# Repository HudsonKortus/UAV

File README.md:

<div align="center">
    
</div>

# UAV 2.0
UAV 2.0 is a thrust vector controlled, electric ducted fan powered UAV. I started this project in June of 2020, and have been working on it off and on ever since. Over the course of this project I have become a better programmer, more confident in CAD, I have learned how to aerodynamically simulate parts in CFD, and taught myself how to make custom PCBs using EAGLE. There is still work that needs to be done to get the UAV to a place where it can fly. 

# ABOUT
The UAV utilizes moveable thrust vanes which are in the exhaust stream of the electric ducted fan to stabilize the vehicle. The control system is a very basic PID loop, but I plan to move to an LQG controller which will allow the UAV to hover in one place. All the electronics are custom. I used a Teensy 4.0 for the microcontroller, and BMI 088 for the gyroscope and acceleration reading. The electric ducted fan is a basic one I got off Amazon which runs off a 4s, 4000mAh lipo. The electric ducted fan produces a little over 1.2kg of static thrust which currently is not enough to lift the vehicle.

# TODO
 * make UAV be tethered to battery instead of carrying it because the battery is too heavy
 * change form using thrust vanes to gimbaling the motor because thrust vanes cannot be practically mathematically characterizes
 * rewrite code to be more object oriented
 * replace the PID controller with an LQG controller
 * make FAA compliant

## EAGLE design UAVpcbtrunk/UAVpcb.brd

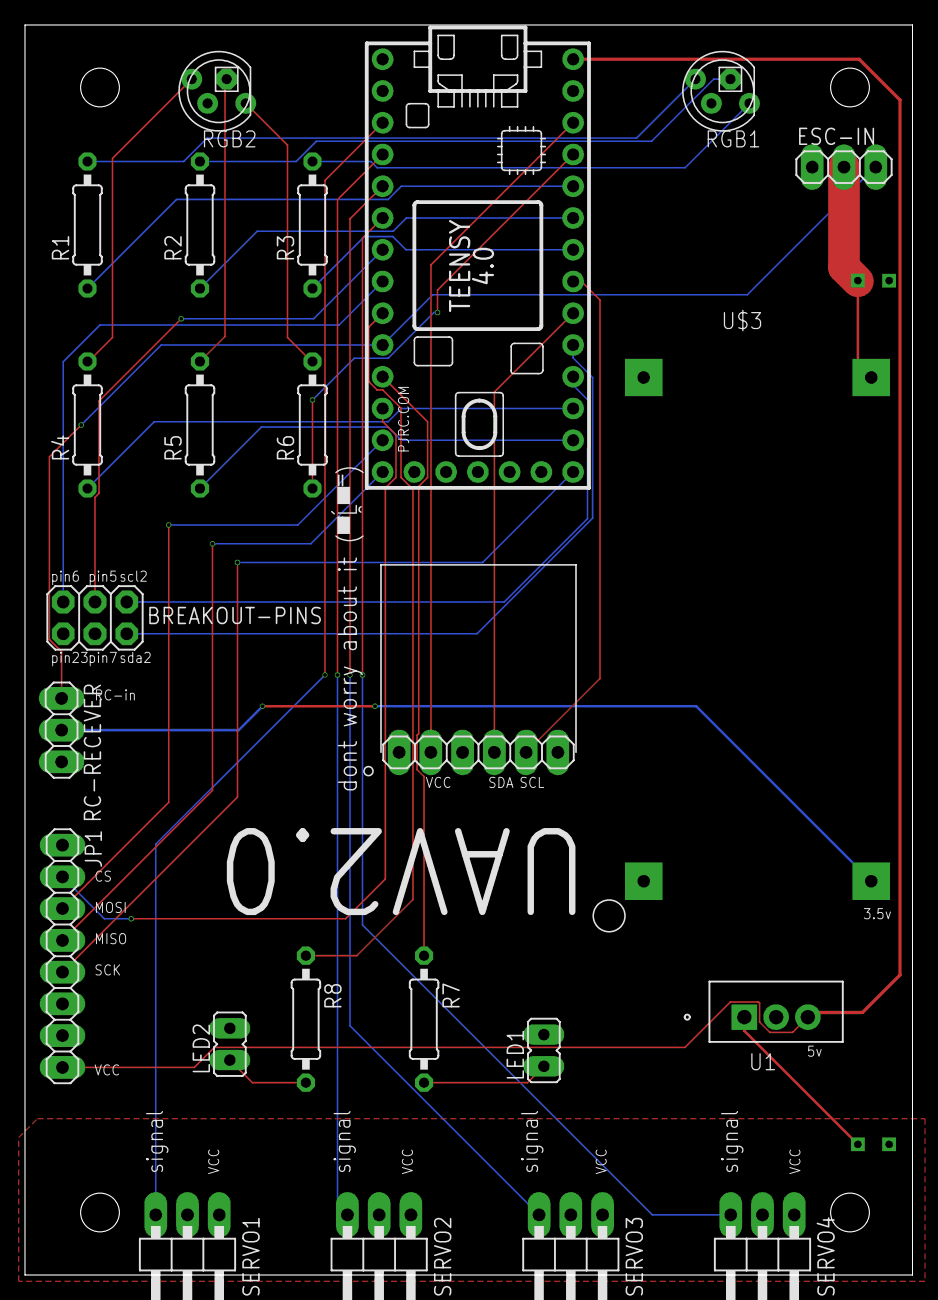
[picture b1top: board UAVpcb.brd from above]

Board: 2 copper layers, 71.0 x 100.0 mm, 25 parts (1 on the bottom side), 37 nets.

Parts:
BREAKOUT-PINS: 2X03
ESC-IN: 1X03
JP1: 1X08
LED1, LED2: LED2P; JP1
R1, R2, R3, R4, R5, R6, R7, R8: 220; 0207/10
RC-RECEVER: 1X03
RGB1, RGB2: 5MMRGBLED; LED5MMRGB
SERVO1, SERVO2, SERVO3, SERVO4: 1X03/90
U1: L7805CV; TO-220_STM
U$1: TEENSY_4.0
U$2: BMI088; 1X06
U$3: LM2596
U$4: AT35

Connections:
3.3V: U$1.3V3_LO, U$2.2
3.5V: RC-RECEVER.2, U$3.P$2
5.5V: ESC-IN.2, U$3.P$3, U$4.IN+
5V: JP1.8, U1.3, U$1.VIN
6V: SERVO1.2, SERVO2.2, SERVO3.2, SERVO4.2, U1.1, U$4.VO+
BLUE1: R3.1, U$1.20/A6
BLUE2: R6.1, U$1.23/A9
CS: JP1.2, U$1.10/CS
GND: ESC-IN.1, JP1.6, LED1.2, LED2.2, RC-RECEVER.3, RGB1.3, RGB2.3, SERVO1.1, SERVO2.1, SERVO3.1, SERVO4.1, U1.2, U$1.GND, U$2.3, U$3.P$1, U$3.P$4, U$4.IN-, U$4.VO-
GREEN1: R2.1, U$1.21/A7
GREEN2: R5.1, U$1.14/A0
LED1: R7.1, U$1.9/CS
LED2: R8.1, U$1.7
MISO: JP1.4, U$1.12/MISO
MOSI: JP1.3, U$1.11/MOSI
unnamed: LED1.1, R7.2
unnamed: LED2.1, R8.2
unnamed: R6.2, RGB2.1
unnamed: R5.2, RGB2.2
unnamed: R4.2, RGB2.4
unnamed: R3.2, RGB1.1
unnamed: R2.2, RGB1.2
unnamed: R1.2, RGB1.4
RC-SIGNAL: ESC-IN.3, RC-RECEVER.1, U$1.8
RED1: R1.1, U$1.22/A8
RED2: R4.1, U$1.15/A1
SCK: JP1.5, U$1.13/SCK
SCL: U$1.19/A5/SCL, U$2.5
SCL2: BREAKOUT-PINS.1, U$1.16/A2
SDA: U$1.18/A4/SDA, U$2.4
SDA2: BREAKOUT-PINS.2, U$1.17/A3
SERVO1SIGNAL: SERVO1.3, U$1.1/TX
SERVO2SIGNAL: SERVO2.3, U$1.2
SERVO3SIGNAL: SERVO3.3, U$1.3/CANTX
SERVO4SIGNAL: SERVO4.3, U$1.4/CANRX
TEENSY5: BREAKOUT-PINS.3, U$1.5
TEENSY6: BREAKOUT-PINS.5, U$1.6

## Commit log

2021-12-07 added more pictures and updated the README for 3DModels to be more helpfull
2021-12-07 edited README files to have more information in them
2021-12-07 experamenting with how images appear
2021-12-14 expanded readme files to be more discriptive
2021-12-14 expaded readme files, added image of thrust vane data, and updated thrust vane spreadsheet to make everything easier to read
2021-12-15 updated readme to have more pictures
2022-01-01 Removed unnecessary directory containing thrust vane CFD and edited 3D model's readme.
2022-01-01 edited readme to be more clear and concise.
2022-01-01 fixed link in readme.
2022-01-04 change thumbnail image because it was reduntant
2022-04-01 add pcb files
